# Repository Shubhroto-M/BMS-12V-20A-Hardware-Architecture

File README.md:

12V 20A High-Current Battery Management System (BMS)Role: Hardware & Thermal Architecture
Status: V0.2 Blueprint Complete (Validated via Ansys Simulation)

The Objective:

Architected and routed a custom 12V, 20A continuous-draw Battery Management System designed for high-current robotics and electric power applications. The design prioritizes extreme hardware reliability, completely bypassing firmware-dependent microcontrollers in favor of hardware-level fault protection.Core ArchitectureLogic Controller: Texas Instruments BQ77915. Chosen for its standalone, firmware-less hardware protection (Overvoltage, Undervoltage, Overcurrent, and Short-Circuit).Power Gating: Implemented a back-to-back (Source-to-Source) MOSFET topology on the low side. This creates a true bidirectional block, ensuring that charging and discharging paths are completely isolated when a fault state is triggered, preventing body-diode bypass.Transient Protection: Integrated TVS (Transient Voltage Suppression) diodes to armor the board against inductive voltage spikes from motors and reverse-polarity events.The Engineering Challenge: Thermal BottleneckingDuring the initial validation of V0.1, I ran a localized thermal stress test using Ansys Discovery. The simulation revealed a critical failure point under maximum load:Pushing 20 Amps continuously through standard 9.3mΩ SMD MOSFETs generated nearly 4 Watts of localized Joule heating ($I^2R$).Due to the low thermal conductivity of the standard FR4 PCB substrate ($0.3 \text{ W/m·K}$), the heat was unable to dissipate efficiently. The simulation showed theoretical junction temperatures exceeding 595°C—a catastrophic failure state.

The V0.2 Pivot (Solving the Thermal Crisis)Rather than increasing the PCB footprint to accommodate bulky, expensive aluminum heatsinks, I re-engineered the power path at the silicon level.Component Swap: Replaced the generic silicon with premium Infineon BSC010N04LS MOSFETs featuring an ultra-low $R_{DS(on)}$ of 1.0mΩ.The Result: This pivot reduced localized heat generation by nearly 90% (dropping from ~4W down to 0.4W per chip).Final Validation: Rerunning the Ansys simulation with a targeted 0.5mm local fidelity mesh confirmed the fix. The concentrated heat was entirely eliminated, allowing the custom copper pours to passively dissipate the remaining thermal load into the ambient air, peaking at a completely safe 60°C under maximum continuous draw.

Industrial Design & EnclosureTo complete the hardware package, I designed a custom, manufacturable 3D enclosure in Fusion 360. The casing features precision IO cutouts for the high-current screw terminals and JST balancing leads, ensuring a flush fit and mechanical strain relief for the PCB.

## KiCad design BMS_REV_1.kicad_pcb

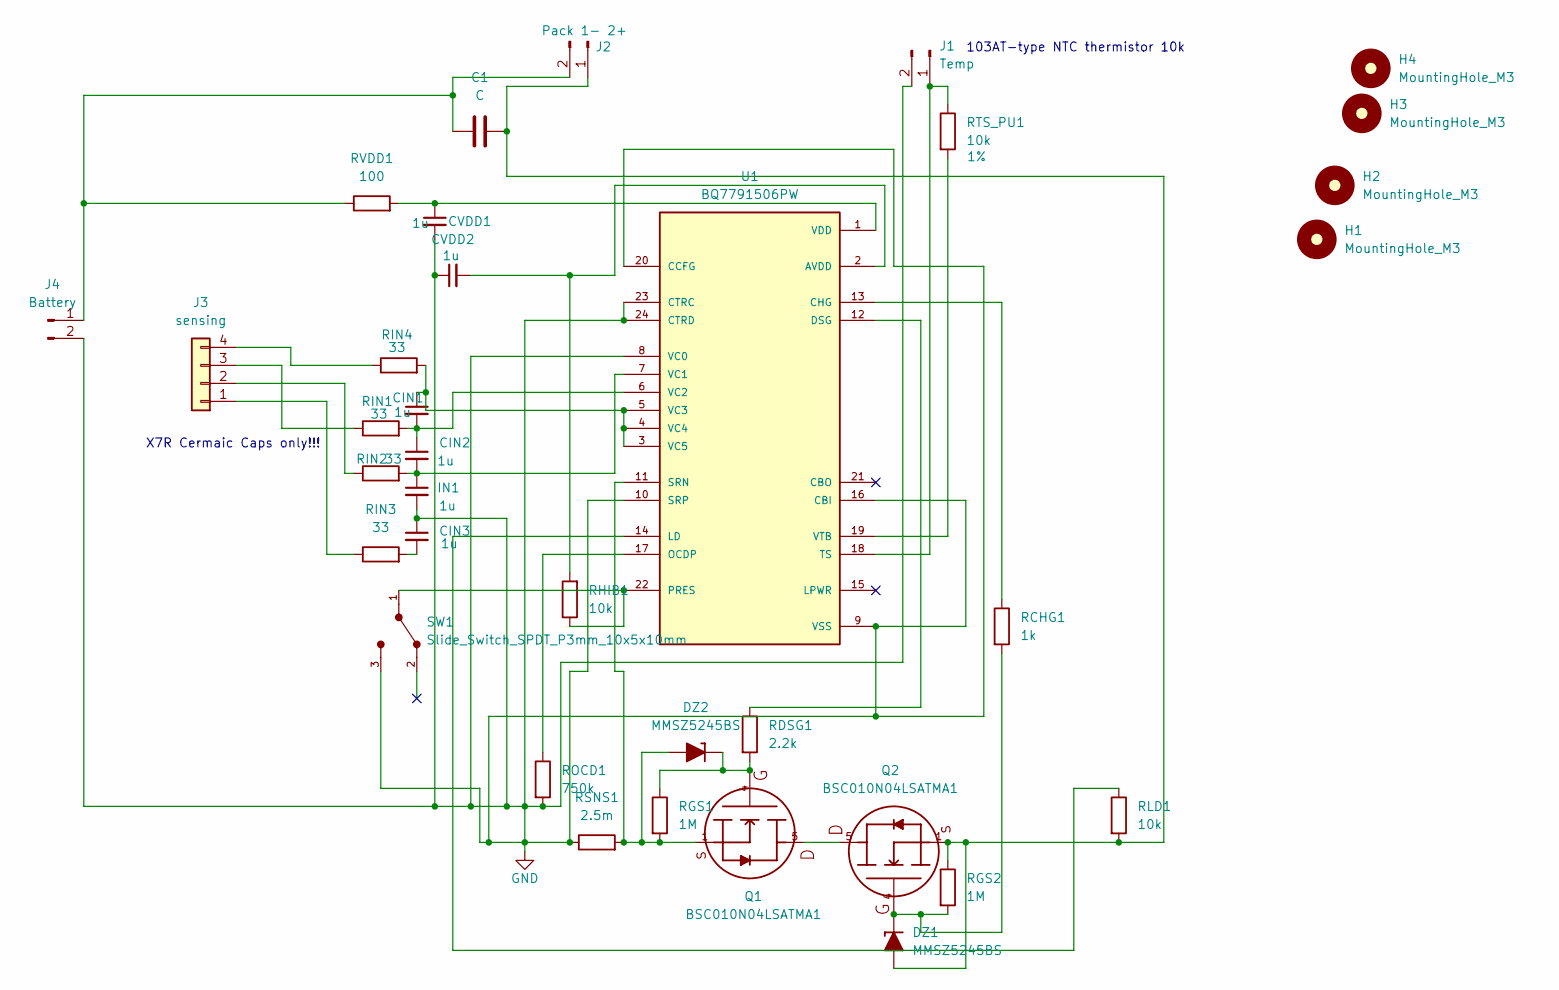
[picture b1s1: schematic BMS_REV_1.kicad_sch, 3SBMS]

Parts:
C1: C; CP_Radial_D10.0mm_P5.00mm
CIN1, CIN2, CIN3: 1u; C_0603_1608Metric; Voltage 1kV; Tolerance 100%
CVDD1, CVDD2: 1u; C_0603_1608Metric; Voltage 1kV; Tolerance 100%
DZ1, DZ2: MMSZ5245BS; D_SOD-323
H1, H2, H3, H4: MountingHole_M3; MountingHole_3.2mm_M3
IN1: 1u; C_0603_1608Metric; Voltage 1kV; Tolerance 100%
J1: Temp; JST_PH_B2B-PH-K_1x02_P2.00mm_Vertical
J2: Pack 1- 2+; TerminalBlock_Phoenix_MKDS-3-2-5.08_1x02_P5.08mm_Horizontal
J3: sensing; JST_XH_B4B-XH-A_1x04_P2.50mm_Vertical; Part Number 1-0401FBV0T
J4: Battery; TerminalBlock_Phoenix_MKDS-3-2-5.08_1x02_P5.08mm_Horizontal
Q1, Q2: BSC010N04LSATMA1; MOSFET_BSC093N04LSGATMA1
RCHG1: 1k; R_0805_2012Metric
RDSG1: 2.2k; R_0805_2012Metric
RGS1, RGS2: 1M; R_0805_2012Metric
RHIB1: 10k; R_0805_2012Metric
RIN1, RIN2, RIN3, RIN4: 33; R_0805_2012Metric
RLD1: 10k; R_0805_2012Metric
ROCD1: 750k; R_0805_2012Metric
RSNS1: 2.5m; R_2512_6332Metric
RTS_PU1: 10k; R_0805_2012Metric; Tolerance 1%
RVDD1: 100; R_0805_2012Metric
SW1: Slide_Switch_SPDT_P3mm_10x5x10mm
U1: BQ7791506PW; TSSOP-24_4.4x7.8mm_P0.65mm; PARTREV H; DigiKey_Part_Number 296-BQ7791506PW-ND

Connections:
GND: CIN3.1, CVDD1.2, CVDD2.1, IN1.2, J1.2, J4.2, ROCD1.2, RSNS1.1, SW1.3, U1.8 (VC0), U1.9 (VSS), U1.10 (SRP), U1.16 (CBI), U1.20 (CCFG), U1.23 (CTRC), U1.24 (CTRD)
unnamed: CIN3.2, RIN3.2
unnamed: C1.2, DZ1.2 (A), J2.1, Q2.1, Q2.2, Q2.3, RGS2.1, RLD1.2
unnamed: DZ1.1 (K), Q2.4, RCHG1.2, RGS2.2
unnamed: DZ2.2 (A), Q1.1, Q1.2, Q1.3, RGS1.2, RSNS1.2, U1.11 (SRN)
unnamed: DZ2.1 (K), Q1.4, RDSG1.2, RGS1.1
unnamed: J1.1, RTS_PU1.1, U1.18 (TS)
unnamed: C1.1, J2.2, J4.1, RVDD1.1
unnamed: J3.1, RIN3.1
unnamed: J3.2, RIN2.1
unnamed: J3.3, RIN1.1
unnamed: J3.4, RIN4.1
unnamed: Q1.5, Q2.5
unnamed: CVDD2.2, RHIB1.2, U1.2 (AVDD)
unnamed: RCHG1.1, U1.13 (CHG)
unnamed: RDSG1.1, U1.12 (DSG)
unnamed: RLD1.1, U1.14 (LD)
unnamed: ROCD1.1, U1.17 (OCDP)
unnamed: RHIB1.1, SW1.1, U1.22 (PRES)
unnamed: CIN2.2, IN1.1, RIN2.2, U1.7 (VC1)
unnamed: CIN1.2, CIN2.1, RIN1.2, U1.6 (VC2)
unnamed: CIN1.1, RIN4.2, U1.3 (VC5), U1.4 (VC4), U1.5 (VC3)
unnamed: CVDD1.1, RVDD1.2, U1.1 (VDD)
unnamed: RTS_PU1.2, U1.19 (VTB)

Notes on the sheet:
X7R Cermaic Caps only!!!
103AT-type NTC thermistor 10k

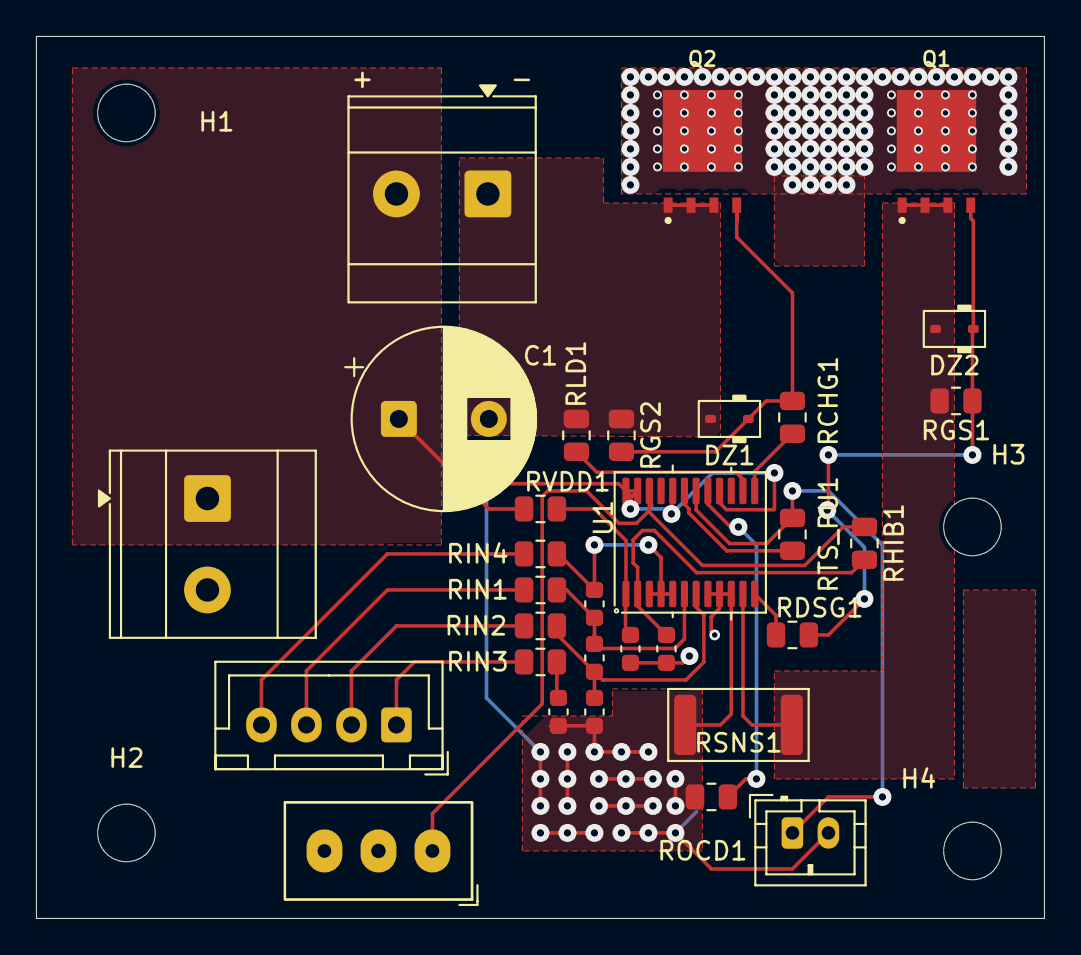
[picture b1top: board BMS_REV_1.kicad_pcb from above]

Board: 2 copper layers, 56.0 x 49.0 mm, 35 parts (0 on the bottom side), 24 nets.
